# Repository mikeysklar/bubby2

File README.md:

# bubby2
pocket chording keyboard

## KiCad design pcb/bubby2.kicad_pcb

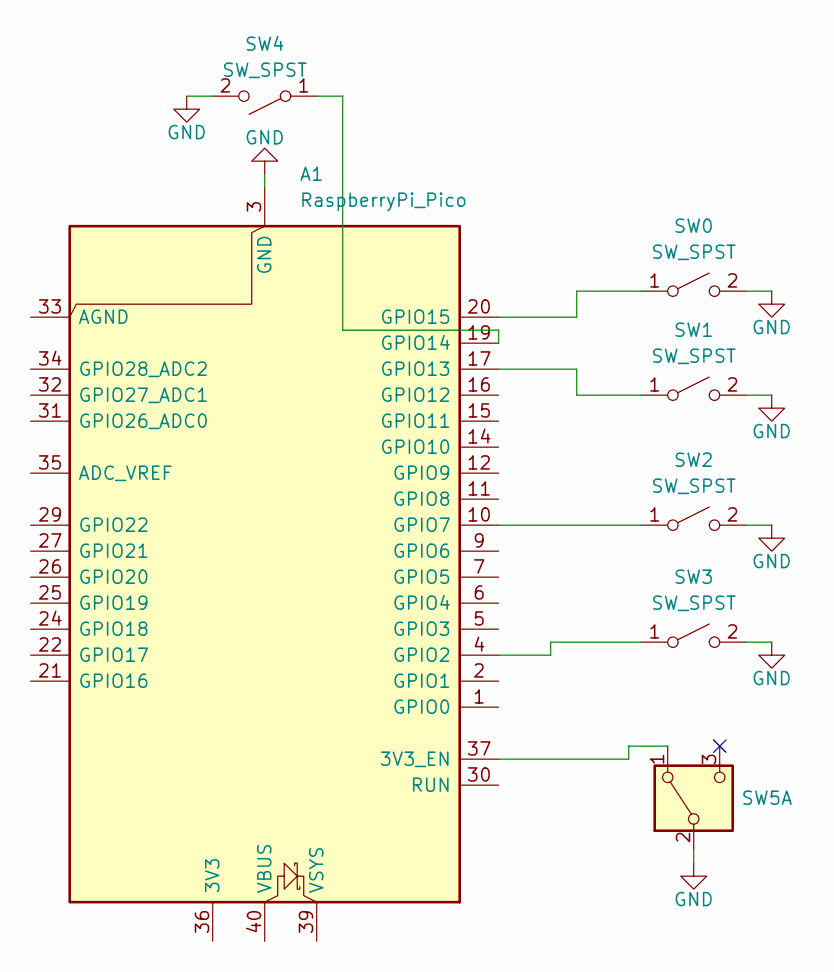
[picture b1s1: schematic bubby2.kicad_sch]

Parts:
A1: RaspberryPi_Pico; RaspberryPi_Pico_SMD
SW0, SW1, SW2, SW3, SW4: SW_SPST; Panasonic_EVQPUL_EVQPUC
SW5: SW_DPDT_x2; Untitled

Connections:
GND: A1.3 (GND), A1.8 (GND), A1.13 (GND), A1.18 (GND), A1.23 (GND), A1.28 (GND), A1.38 (GND), SW0.2 (B), SW1.2 (B), SW2.2 (B), SW3.2 (B), SW4.2 (B), SW5.2 (B)
unnamed: A1.37 (3V3_EN), SW5.1 (A)
unnamed: A1.4 (GPIO2), SW3.1 (A)
unnamed: A1.10 (GPIO7), SW2.1 (A)
unnamed: A1.17 (GPIO13), SW1.1 (A)
unnamed: A1.19 (GPIO14), SW4.1 (A)
unnamed: A1.20 (GPIO15), SW0.1 (A)

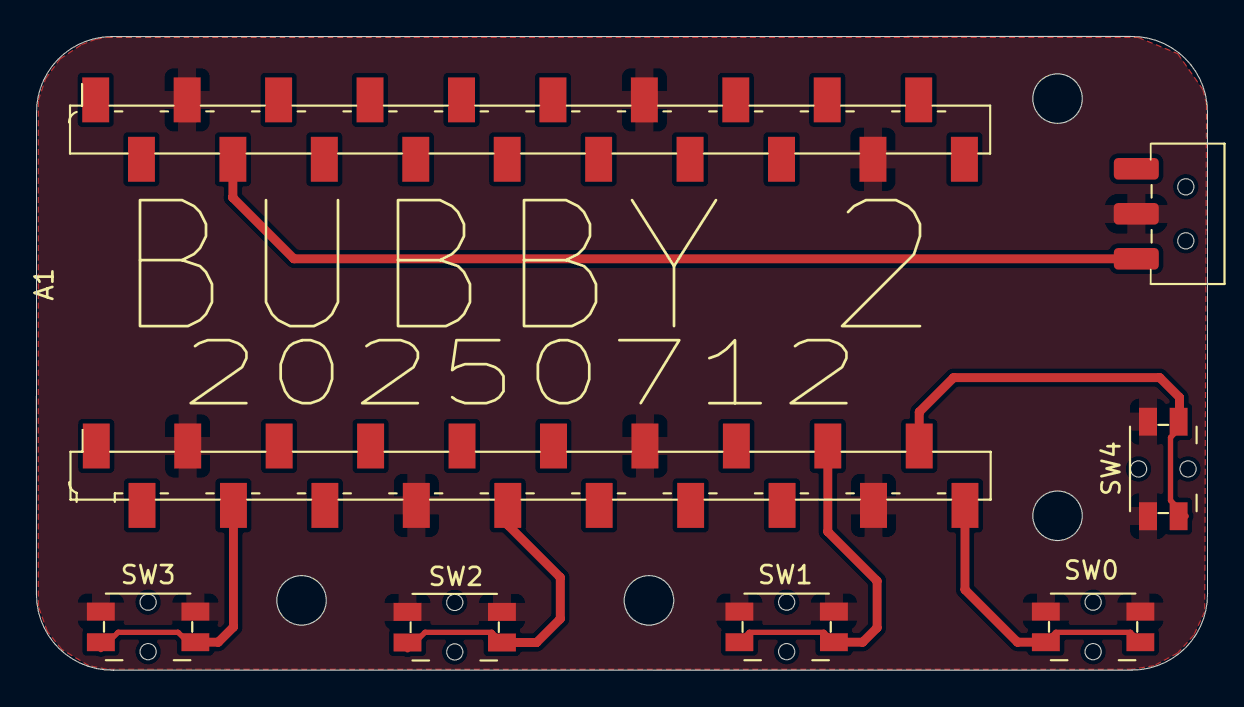
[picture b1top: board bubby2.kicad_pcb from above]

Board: 2 copper layers, 65.1 x 35.2 mm, 7 parts (0 on the bottom side), 7 nets.

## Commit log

2025-07-01 sch / pcb / 3d setup
2025-07-02 pcb routed
2025-07-03 pretty close
2025-07-04 no DRC errors!
    changed schematic parts to remove all DRC issues.
2025-07-05 case / mount hole move
2025-07-05 cad top cover
    risers, alignment
2025-07-05 current pcb
2025-07-06 cleaned up files
2025-07-07 pcb / cad
    adjusting case buttons
2025-07-12 minor fit changes
    moved a button, added a screw hole...
2025-07-14 good place
    * buttons work
    * pcb good
    * case fit good
    * adding in chording code
2025-07-14 pics
2025-07-14 surprise
    This code just worked. A few button remaps from cinco-cinco and I see all 7 layers.
    Adding display support.
2025-07-15 simple screen works!
    minimal code, black background, magenta text...took a while to figure out the display settings.
2025-07-15 working chords on screen
2025-07-15 chord / screen
    working well, got line wrap and nice font. 18wpm in monkeytype on first test.
2025-07-15 lowercase on led
    fixed case on screen
2025-07-25 bat / hid
    * runs on battery (1000mAh)
    * HID toggle support (0,1,2,3,4) layer 3
